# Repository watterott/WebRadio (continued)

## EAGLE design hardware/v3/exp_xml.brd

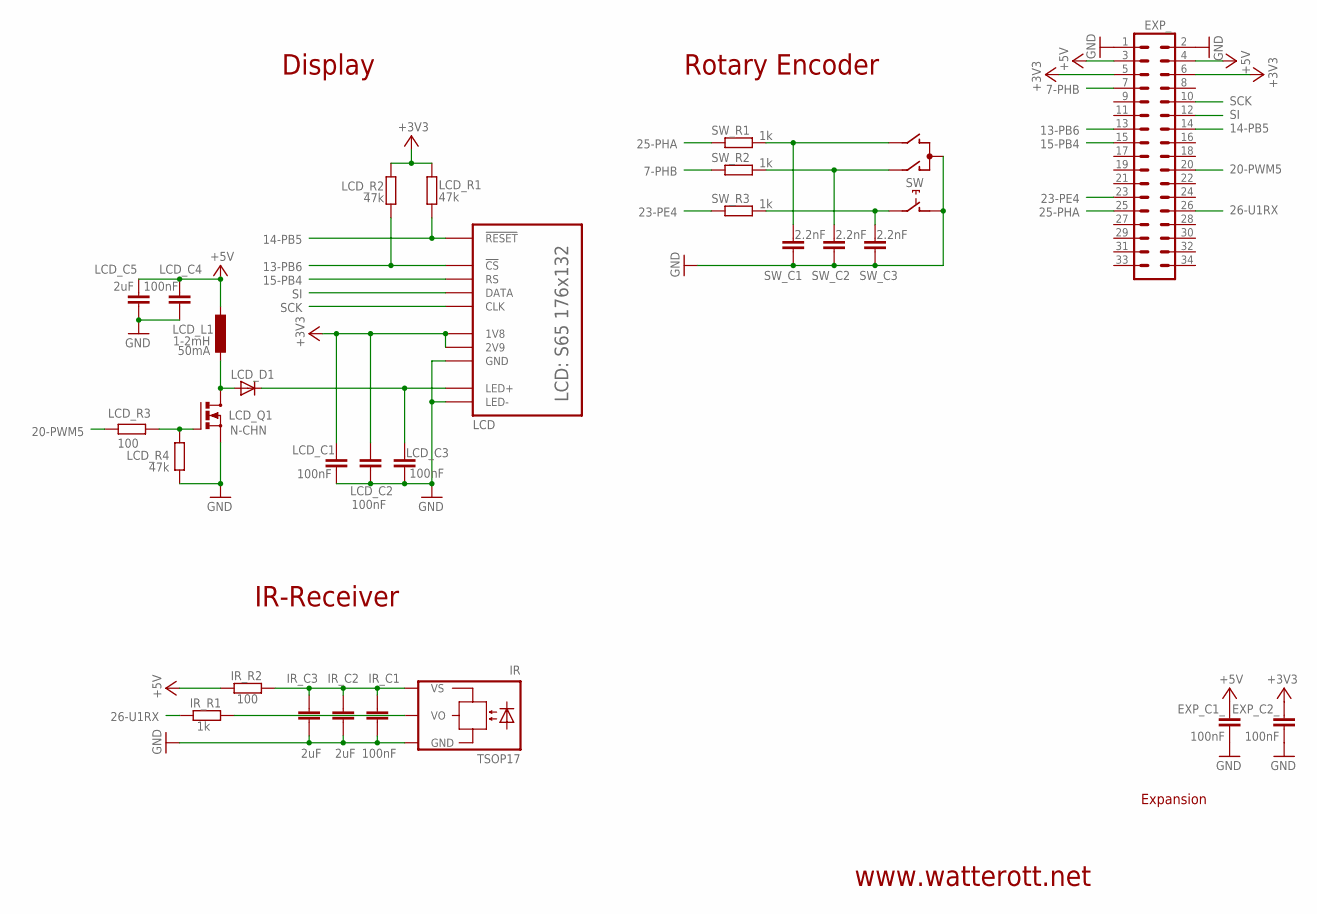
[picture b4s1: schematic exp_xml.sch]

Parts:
EXP_: MA17-2
EXP_C1_, EXP_C2_: 100nF; C0603
IR: TSOP17
IR_C1: 100nF; C0603
IR_C2, IR_C3: 2uF; C0603K
IR_R1: 1k; R0603
IR_R2: 100; R0603
LCD: S65
LCD_C1, LCD_C2, LCD_C3, LCD_C4: 100nF; C0603
LCD_C5: 2uF; C0603K
LCD_D1: DIODE-DO214AA; DO214AA
LCD_L1: 1-2mH; L4532M
LCD_Q1: N-CHN; MICRO3
LCD_R1, LCD_R2, LCD_R4: 47k; R0603
LCD_R3: 100; R0603
SW: EC12E_SW; ALPS_EC12E_SW
SW_C1, SW_C2, SW_C3: 2.2nF; C0603
SW_R1, SW_R2, SW_R3: 1k; R0603

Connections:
7-PHB: EXP_.7, SW_R2.2
13-PB6: EXP_.13, LCD.CS (!CS), LCD_R2.2
14-PB5: EXP_.14, LCD.RESET (!RESET), LCD_R1.2
15-PB4: EXP_.15, LCD.RS
20-PWM5: EXP_.20, LCD_R3.2
23-PE4: EXP_.23, SW_R3.2
25-PHA: EXP_.25, SW_R1.2
26-U1RX: EXP_.26, IR_R1.2
+3V3: EXP_.5, EXP_.6, EXP_C2_.1, LCD.1V8, LCD.2V9, LCD_C1.1, LCD_C2.1, LCD_R1.1, LCD_R2.1
+5V: EXP_.3, EXP_.4, EXP_C1_.1, IR_R2.2, LCD_C4.1, LCD_C5.1, LCD_L1.2
B: LCD_Q1.1 (G), LCD_R3.1, LCD_R4.2
E: LCD_D1.A, LCD_L1.1, LCD_Q1.3 (D)
GND: EXP_.1, EXP_.2, EXP_C1_.2, EXP_C2_.2, IR.GND, IR_C1.2, IR_C2.2, IR_C3.2, LCD.GND, LCD.LED-, LCD_C1.2, LCD_C2.2, LCD_C3.2, LCD_C4.2, LCD_C5.2, LCD_Q1.2 (S), LCD_R4.1, SW.C, SW.D (1), SW_C1.1, SW_C2.1, SW_C3.1
LED+: LCD.LED+, LCD_C3.1, LCD_D1.C
unnamed: SW.B, SW_C1.2, SW_R1.1
unnamed: SW.A, SW_C2.2, SW_R2.1
unnamed: SW.E (2), SW_C3.2, SW_R3.1
SCK: EXP_.10, LCD.CLK
SI: EXP_.12, LCD.DATA
VO: IR.VO, IR_R1.1
VS: IR.VS, IR_C1.1, IR_C2.1, IR_C3.1, IR_R2.1

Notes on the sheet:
Display
Rotary Encoder
Expansion
www.watterott.net
50mA
IR-Receiver

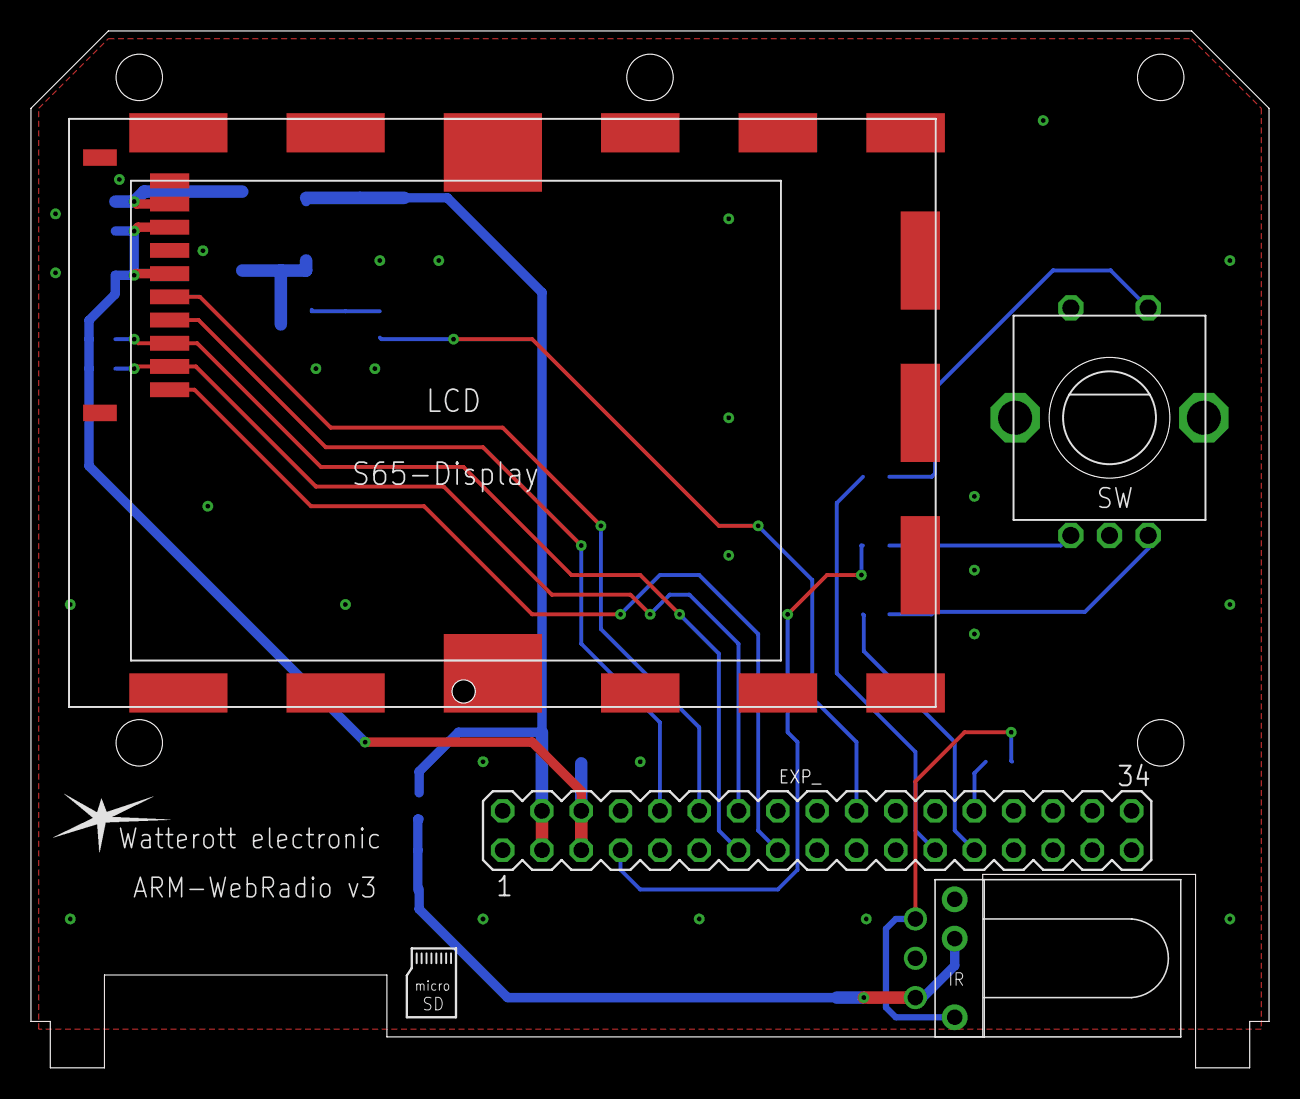
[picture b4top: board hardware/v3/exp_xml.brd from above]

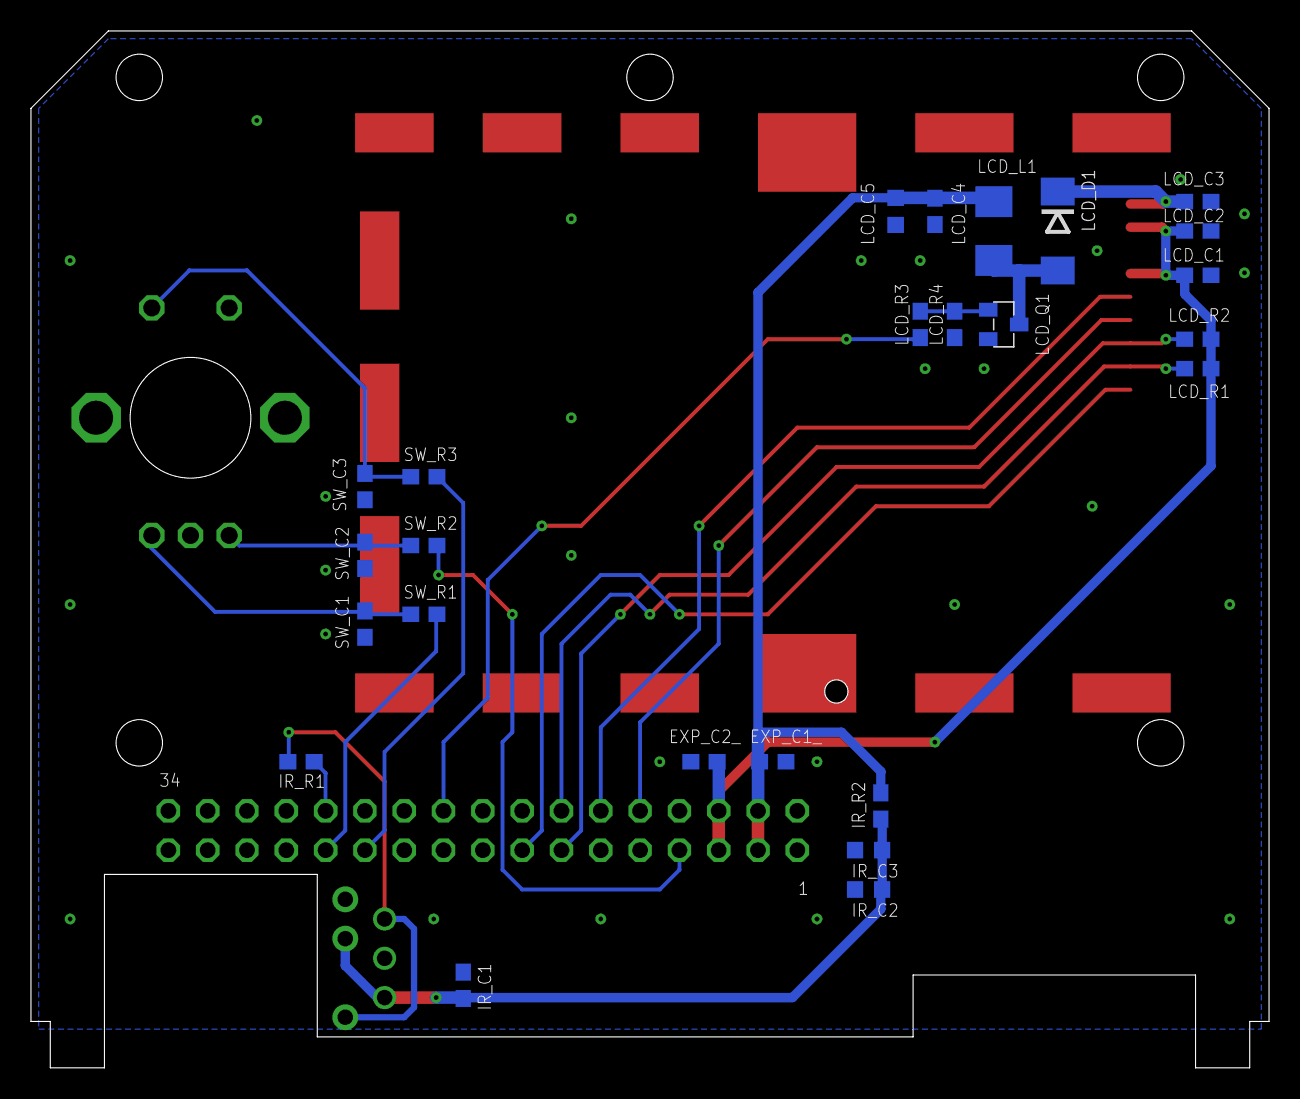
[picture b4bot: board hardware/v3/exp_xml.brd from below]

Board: 2 copper layers, 80.0 x 67.0 mm, 29 parts (25 on the bottom side), 21 nets.

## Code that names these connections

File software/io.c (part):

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{
  //GPIO A: VS
  SysCtlPeripheralEnable(SYSCTL_PERIPH_GPIOA);
  GPIOSetInput(GPIO_PORTA_BASE, GPIO_PIN_1 | GPIO_PIN_4); //VS_SO, VS_DREQ = input
  GPIOSetOutput(GPIO_PORTA_BASE, GPIO_PIN_2 | GPIO_PIN_3 | GPIO_PIN_5 | GPIO_PIN_6 | GPIO_PIN_7); //VS_SCK, VS_DCS, VS_SI, VS_CS, VS_RST = output
  GPIOPinWrite(GPIO_PORTA_BASE, GPIO_PIN_2 | GPIO_PIN_3 | GPIO_PIN_5 | GPIO_PIN_6 | GPIO_PIN_7, GPIO_PIN_3 | GPIO_PIN_6); //VS_SCK, VS_SI, VS_RST = low / VS_DCS, VS_CS = high
  GPIOPinTypeSSI(GPIO_PORTA_BASE, GPIO_PIN_2 | GPIO_PIN_4 | GPIO_PIN_5); //VS_SCK, VS_SO, VS_SI = ssi

  //GPIO B: SD, LCD
  SysCtlPeripheralEnable(SYSCTL_PERIPH_GPIOB);
  GPIOSetOutput(GPIO_PORTB_BASE, GPIO_PIN_0 | GPIO_PIN_1 | GPIO_PIN_4 | GPIO_PIN_5 | GPIO_PIN_6); //SD_PWR, SD_CS, LCD_RS, LCD_RST, LCD_CS -> ouput
  GPIOPinWrite(GPIO_PORTB_BASE, GPIO_PIN_0 | GPIO_PIN_1 | GPIO_PIN_4 | GPIO_PIN_5 | GPIO_PIN_6, GPIO_PIN_1 | GPIO_PIN_4 | GPIO_PIN_6); //SD_PWR, VS_RST = low / SD_CS, LCD_RS, LCD_CS = high

  //GPIO C: JTAG
#if defined LM3S_REV_A1 || defined LM3S_REV_A2 //for rev A1 & A2 set JTAG pullups on
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  //GPIO E: LCD, SD, F-RAM, Switch
  SysCtlPeripheralEnable(SYSCTL_PERIPH_GPIOE);
  GPIOSetInput(GPIO_PORTE_BASE, GPIO_PIN_2 | GPIO_PIN_4); //SO, SW = input
  GPIOSetOutput(GPIO_PORTE_BASE, GPIO_PIN_0 | GPIO_PIN_1 | GPIO_PIN_3 | GPIO_PIN_7); //SCK, FM_CS, SI, LCD_PWM = output
  GPIOPinWrite(GPIO_PORTE_BASE, GPIO_PIN_0 | GPIO_PIN_1 | GPIO_PIN_3 | GPIO_PIN_7, GPIO_PIN_1); //SCK, SI, LCD_PWM = low / FM_CS = high
  GPIOPinTypeSSI(GPIO_PORTE_BASE, GPIO_PIN_0 | GPIO_PIN_2 | GPIO_PIN_3); //SCK, SO, SI = ssi

  //GPIO F: Encoder, USB-Power, Ethernet
  SysCtlPeripheralEnable(SYSCTL_PERIPH_GPIOF);
  GPIOSetInput(GPIO_PORTF_BASE, GPIO_PIN_0); //PHA = input
  GPIOSetOutput(GPIO_PORTF_BASE, GPIO_PIN_2 | GPIO_PIN_3); //LED1, LED2 = output
  GPIOSetOutputOD(GPIO_PORTF_BASE, GPIO_PIN_1); //USB_PWR = open-drain output
  GPIOPinWrite(GPIO_PORTF_BASE, GPIO_PIN_1, GPIO_PIN_1); //USB_PWR = high
  GPIODirModeSet(GPIO_PORTF_BASE, GPIO_PIN_2 | GPIO_PIN_3, GPIO_DIR_MODE_HW); //LED1, LED2 = ethernet

  return;
}
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
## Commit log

2018-09-23 added binaries
2018-09-23 added photos
